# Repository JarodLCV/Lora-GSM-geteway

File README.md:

# **Passerelle LoRa-GSM**  

Un projet combinant des connaissances en électronique et en programmation pour créer un pont entre le GSM et le LoRa.

----

**Table de matières**
- [**Passerelle LoRa-GSM**](#passerelle-lora-gsm)
  - [ℹ️ **Contexte du projet**](#ℹ️-contexte-du-projet)
  - [🗂️ Dossiers](#️-dossiers)
  - [**Réalisation du projet**](#réalisation-du-projet)
    - [**Définitions :**](#définitions-)
  - [Comment continuer le projet](#comment-continuer-le-projet)
  - [Explication du code](#explication-du-code)

----

## ℹ️ **Contexte du projet**

Il s'agit d'un projet du cours de Projet d'Électronique, encadré par Monsieur Christian Peter (<Christian.PETER@univ-cotedazur.fr>), dans le cadre du cursus d'Ingénierie Électronique et Informatique Industrielle de la Polytech de Sophia Antipolis.  
Ce projet consiste à concevoir une ruche connectée, incluant la collecte de données, la transmission de ces données à distance, l’élimination des parasites par laser, etc.  
Cette partie du projet concerne la communication à distance des données et est réalisée par le groupe composé de:
**Guilherme VENTAPANE RODRIGUES** <guilherme@ventapane.eu>
et
**Jarod LECOEUVRE** <jarod.lecoeuvre@etu.univ-cotedazur.fr>

## 🗂️ Dossiers

- 📁 **Compte-rendu** : Les étapes d'avancement du projet et les tâches que chaque membre du groupe avait effectuées.

- 📁 **Partie_Electronique** : Fichiers liés à la partie électronique du projet, tels que le schéma de la carte, la documentation des composants, etc.
  - 📁 **BOM** : Bill of Material de notre projet. La liste des composants nécessaires avec leurs valeurs, pour être placés sur le PCB.
  - 📁 **Documentation_composants** : Fichiers de documentation pour certains composants utilisés dans le projet.
  - 📁 **Eagle_Components** : Composants supplémentaires pour le logiciel EAGLE, qui n'étaient pas présents par défaut et que nous avons dû télécharger pour compléter notre projet.
  - 📁 **Eagle_Schemas** : Schémas que nous avons utilisés pour notre projet, réalisés avec le logiciel EAGLE d'Autodesk.
  - 📁 **Nano to micro simcard adapter 3d** : Un adaptateur de carte SIM vers micro SIM que nous avons imprimé en 3D pour notre projet.
  - 📁 **Anciens_Schemas** : Fichiers de schémas du groupe de l'année dernière.

- 📁 **Partie_Informatique** : Le dossier où se trouve le code qui tourne sur la carte.
  - 📁 **code_groupe_annee_derniere** : Code du projet du groupe de l'année dernière.
  - 📁 **src** : Les fichiers sources de notre projet, où se trouve le fichier main.ino, le fichier principal de notre projet.

## **Réalisation du projet**  

Pour assurer la communication des données sur de longues distances, une passerelle entre LoRa et GSM sera utilisée.  
Cette passerelle sera réalisée à partir d'un circuit imprimé conçu par nous, ainsi que d'un code exécuté sur un **ESP32** connecté à un **SIM7000G**.

Nous nous basons sur le projet de la promotion précédente, réalisé par **Oumar Sadjo Barry & Mor Dieng** / [oumarsadjo / RucherLoRa](https://github.com/oumarsadjo/RucherLoRa)  
<oumar-sadjo.barry@etu.univ-cotedazur.fr> & <mor.dieng@etu.univ-cotedazur.fr>

### **Définitions :**  

**GSM (Global System for Mobile Communications) :**  
C'est un standard de communication mobile utilisé pour la téléphonie cellulaire et la transmission de données. Il permet l’envoi de messages SMS, les appels et la connexion à Internet via **GPRS/EDGE/3G/4G**. Le GSM est largement utilisé pour les dispositifs IoT nécessitant une connectivité dans des environnements sans Wi-Fi.  

**LoRa (Long Range) :**  
C'est une technologie de communication sans fil à longue portée et à faible consommation d'énergie, utilisée pour connecter des dispositifs IoT aux réseaux LPWAN (**Low Power Wide Area Network**). LoRa permet de transmettre de petits paquets de données sur de longues distances (jusqu'à 15 km en zones rurales) avec une consommation d’énergie minimale.  

**ESP32 :**  
C'est un microcontrôleur développé par Espressif, intégrant **Wi-Fi et Bluetooth**, ainsi que plusieurs broches **GPIO** pour les capteurs et modules externes. Il est largement utilisé dans les projets IoT grâce à sa connectivité, sa puissance et son faible coût.  

**SIM7000 :**  
C'est un module de communication **GSM/GPRS/NB-IoT/LTE Cat-M1** développé par Simcom. Il permet aux dispositifs IoT d'envoyer et de recevoir des données via les réseaux mobiles, en prenant en charge les connexions **basse consommation**, idéales pour les capteurs distants et les applications de surveillance.  

## Comment continuer le projet

Il reste encore à :
- [ ] Finaliser le débogage de la carte pour établir une communication stable entre les composants ;
- [ ] Intégrer la partie LoRa ;
- [ ] Optimiser la consommation énergétique de la passerelle, pour un usage autonome sur batterie.

## Explication du code

La bibliothèque utilise la communication série (UART) pour envoyer des commandes AT au module GSM. En interne, elle structure ces commandes de façon organisée, permettant au développeur de simplement appeler des fonctions comme modem.gprsConnect() ou modem.sendSMS(), au lieu d’écrire manuellement des lignes du type `AT+CGDCONT=1`,"IP","internet".

TinyGSM est également optimisée pour fonctionner sur des cartes à faible mémoire (d’où le “Tiny” dans son nom), ce qui la rend efficace même sur des microcontrôleurs limités comme l’Arduino Uno.

Analyse du code et explication des parties principales

Le code de notre projet est organisé en plusieurs étapes : configuration, initialisation du modem, choix des modes réseau, test de la connexion GPRS, et envoi de SMS. Voici un résumé des parties essentielles :

Définition du modem et configuration initiale
Au début du code, on définit le type de modem utilisé :

``` CPP
#define TINY_GSM_MODEM_SIM7000
#define TINY_GSM_RX_BUFFER 1024
#define SerialAT Serial1
```

Ces lignes informent la bibliothèque qu’on utilise un SIM7000. On augmente aussi la taille du buffer de réception à 1024 octets, ce qui est utile pour traiter des réponses longues du modem.

Il y a aussi l’option suivante :

``` CPP
#define DUMP_AT_COMMANDS
```

Cela permet d’afficher toutes les commandes AT envoyées et les réponses reçues. C’est très utile pour déboguer si quelque chose ne fonctionne pas comme prévu.

Paramètres pour le réseau mobile

``` CPP
const char apn[]  = "sl2sfr";
const char gprsUser[] = "";
const char gprsPass[] = "";
```

Ici, on entre les informations nécessaires pour se connecter au réseau mobile. L’APN dépend de l’opérateur utilisé. Dans notre cas, c’est “sl2sfr” car nous utilisons un SIM de SFR.

Initialisation du modem

Dans la fonction setup(), on initialise la communication série avec le modem :

``` CPP
SerialAT.begin(UART_BAUD, SERIAL_8N1, PIN_RX, PIN_TX);
```

Ensuite, on redémarre le modem avec `modem.restart()` et on vérifie si tout s’est bien passé.

On récupère aussi quelques infos utiles :

``` CPP
String name = modem.getModemName();
String modemInfo = modem.getModemInfo();
```

Cela permet d’afficher le nom du modem et quelques infos techniques pour s’assurer que le module est bien reconnu.

Configuration du mode réseau

Dans la `loop()`, on configure le mode de fonctionnement du modem :

``` CPP
modem.sendAT("+CFUN=0"); // désactive le modem temporairement
modem.setNetworkMode(2); // mode automatique
modem.setPreferredMode(1); // priorité au mode CAT-M
modem.sendAT("+CFUN=1"); // réactive le modem
```

Ces commandes AT permettent de choisir comment le modem va chercher le réseau (LTE, GSM, NB-IoT, etc.).

Connexion GPRS

Une fois le modem prêt, on tente de se connecter au réseau mobile :

``` CPP
modem.gprsConnect(apn, gprsUser, gprsPass);
```

Après la connexion, on peut vérifier le signal, l’opérateur, l’IMEI, l’adresse IP locale, etc.

Envoi de SMS

À la fin du code, il y a une partie pour tester l’envoi de SMS :

``` CPP
modem.sendSMS(SMS_TARGET, String("Hello from ") + imei);
```

C’est un test simple qui envoie un message contenant l’IMEI du module à un numéro prédéfini.

Mise hors tension et sommeil profond

Enfin, on met le modem hors tension et on fait entrer l’ESP32 en mode sommeil profond pour économiser l’énergie :

``` CPP
modem.poweroff();
esp_deep_sleep_start();
```

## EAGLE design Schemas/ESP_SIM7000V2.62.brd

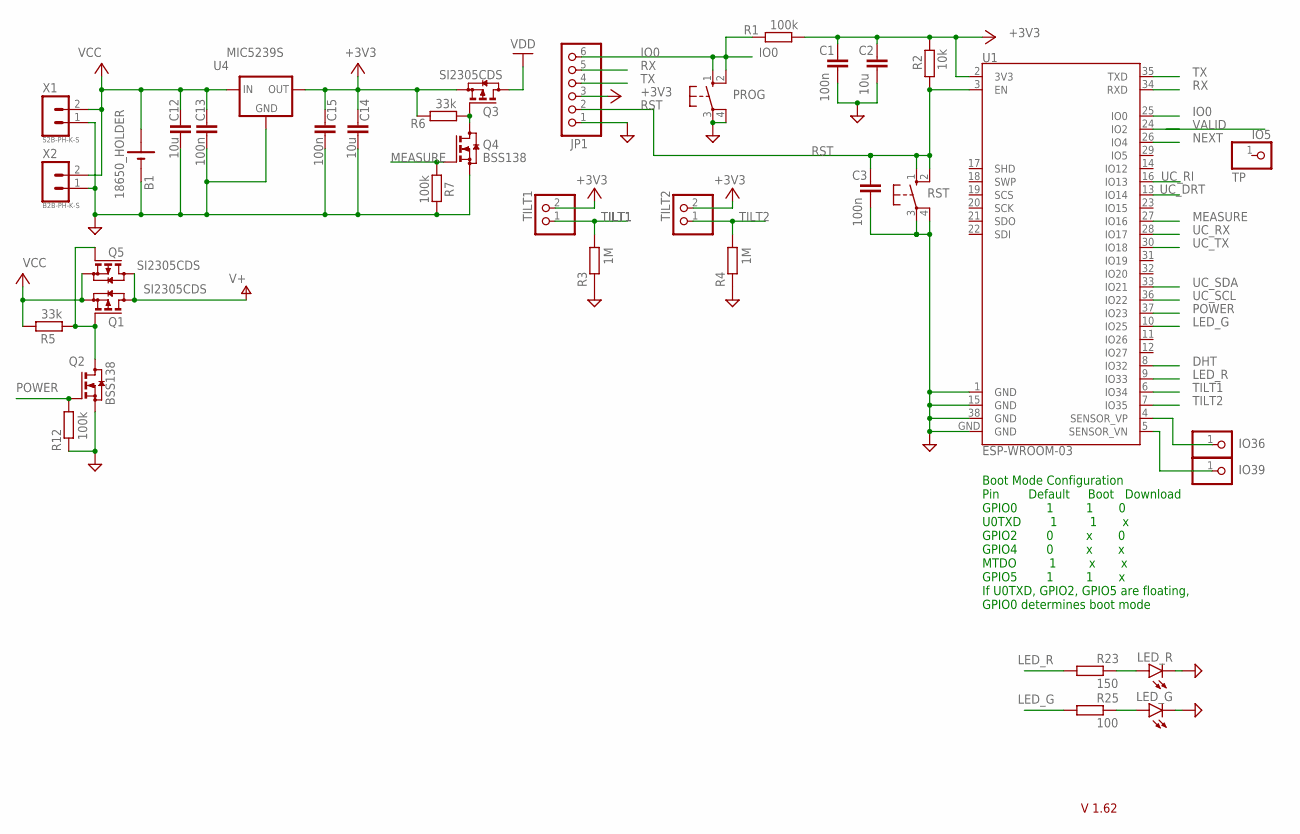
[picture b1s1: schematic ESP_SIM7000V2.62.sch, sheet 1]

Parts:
B1: 18650_HOLDER; 18650
C1, C3, C13, C15: 100n; C1206
C2, C12, C14: 10u; C1210
IO5: TP; 1X01
IO36, IO39: PINHD-1X1; 1X01
JP1: PINHD-1X6; 1X06
LED_G: LEDSMT1206; 1206
LED_R: LEDSMT1206; 1206
PROG: 10-XX; B3F-10XX
Q1, Q3, Q5: SI2305CDS; SOT23
Q2, Q4: BSS138; SOT23
R1, R7, R12: 100k; R1206
R2: 10k; R1206
R3, R4: 1M; R1206
R5, R6: 33k; R1206
R23: 150; R1206
R25: 100; R1206
RST: 10-XX; B3F-10XX
TILT1, TILT2: PINHD-1X2; 1X02
U1: ESP-WROOM-03
U4: MIC5239S; SOT223
X1: S2B-PH-K-S
X2: B2B-PH-K-S

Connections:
+3V3: C1.1, C2.1, C14.1, C15.1, JP1.3, Q3.2 (S), R1.1, R2.2, R6.2, TILT1.2, TILT2.2, U1.2 (3V3), U4.3 (OUT); also elsewhere on the board
DHT: U1.8 (IO32)
GND: B1.-, C1.2, C2.2, C3.2, C12.2, C13.2, C14.2, C15.2, JP1.1, LED_G.C, LED_R.C, PROG.3, PROG.4 (P1), Q2.2 (S), Q4.2 (S), R3.2, R4.2, R7.2, R12.2, RST.3, RST.4 (P1), U1.1 (GND), U1.15 (GND), U1.38 (GND), U1.GND, U4.2 (GND), U4.4 (GND), X1.1, X2.1; also elsewhere on the board
IO0: JP1.6, PROG.1 (S), PROG.2 (S1), R1.2, U1.25 (IO0)
IO36: IO36.1, U1.4 (SENSOR_VP)
IO39: IO39.1, U1.5 (SENSOR_VN)
LED_G: R25.1, U1.10 (IO25)
LED_R: R23.1, U1.9 (IO33); also elsewhere on the board
MEASURE: Q4.1 (G), R7.1, U1.27 (IO16)
unnamed: Q1.1 (G), Q2.3 (D), Q5.1 (G), R5.1
unnamed: Q3.1 (G), Q4.3 (D), R6.1
unnamed: LED_R.A, R23.2
unnamed: LED_G.A, R25.2
unnamed: IO5.1, U1.29 (IO5)
NEXT: U1.26 (IO4)
POWER: Q2.1 (G), R12.1, U1.37 (IO23)
RST: C3.1, JP1.2, R2.1, RST.1 (S), RST.2 (S1), U1.3 (EN)
RX: JP1.5, U1.34 (RXD)
TILT1: R3.1, TILT1.1, U1.6 (IO34)
TILT2: R4.1, TILT2.1, U1.7 (IO35)
TX: JP1.4, U1.35 (TXD)
UC_DRT: U1.13 (IO14); also elsewhere on the board
UC_RI: U1.16 (IO13); also elsewhere on the board
UC_RX: U1.28 (IO17); also elsewhere on the board
UC_SCL: U1.36 (IO22); also elsewhere on the board
UC_SDA: U1.33 (IO21); also elsewhere on the board
UC_TX: U1.30 (IO18); also elsewhere on the board
V+: Q1.3 (D), Q5.3 (D); also elsewhere on the board
VALID: U1.24 (IO2)
VCC: B1.+, C12.1, C13.1, Q1.2 (S), Q5.2 (S), R5.2, U4.1 (IN), X1.2, X2.2
VDD: Q3.3 (D)

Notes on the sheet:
Boot Mode Configuration Pin Default Boot Download GPIO0 1 1 0 U0TXD 1 1 x GPIO2 0 x 0 GPIO4 0 x x MTDO 1 x x GPIO5 1 1 x If U0TXD, GPIO2, GPIO5 are floating, GPIO0 determines boot mode
V 1.62

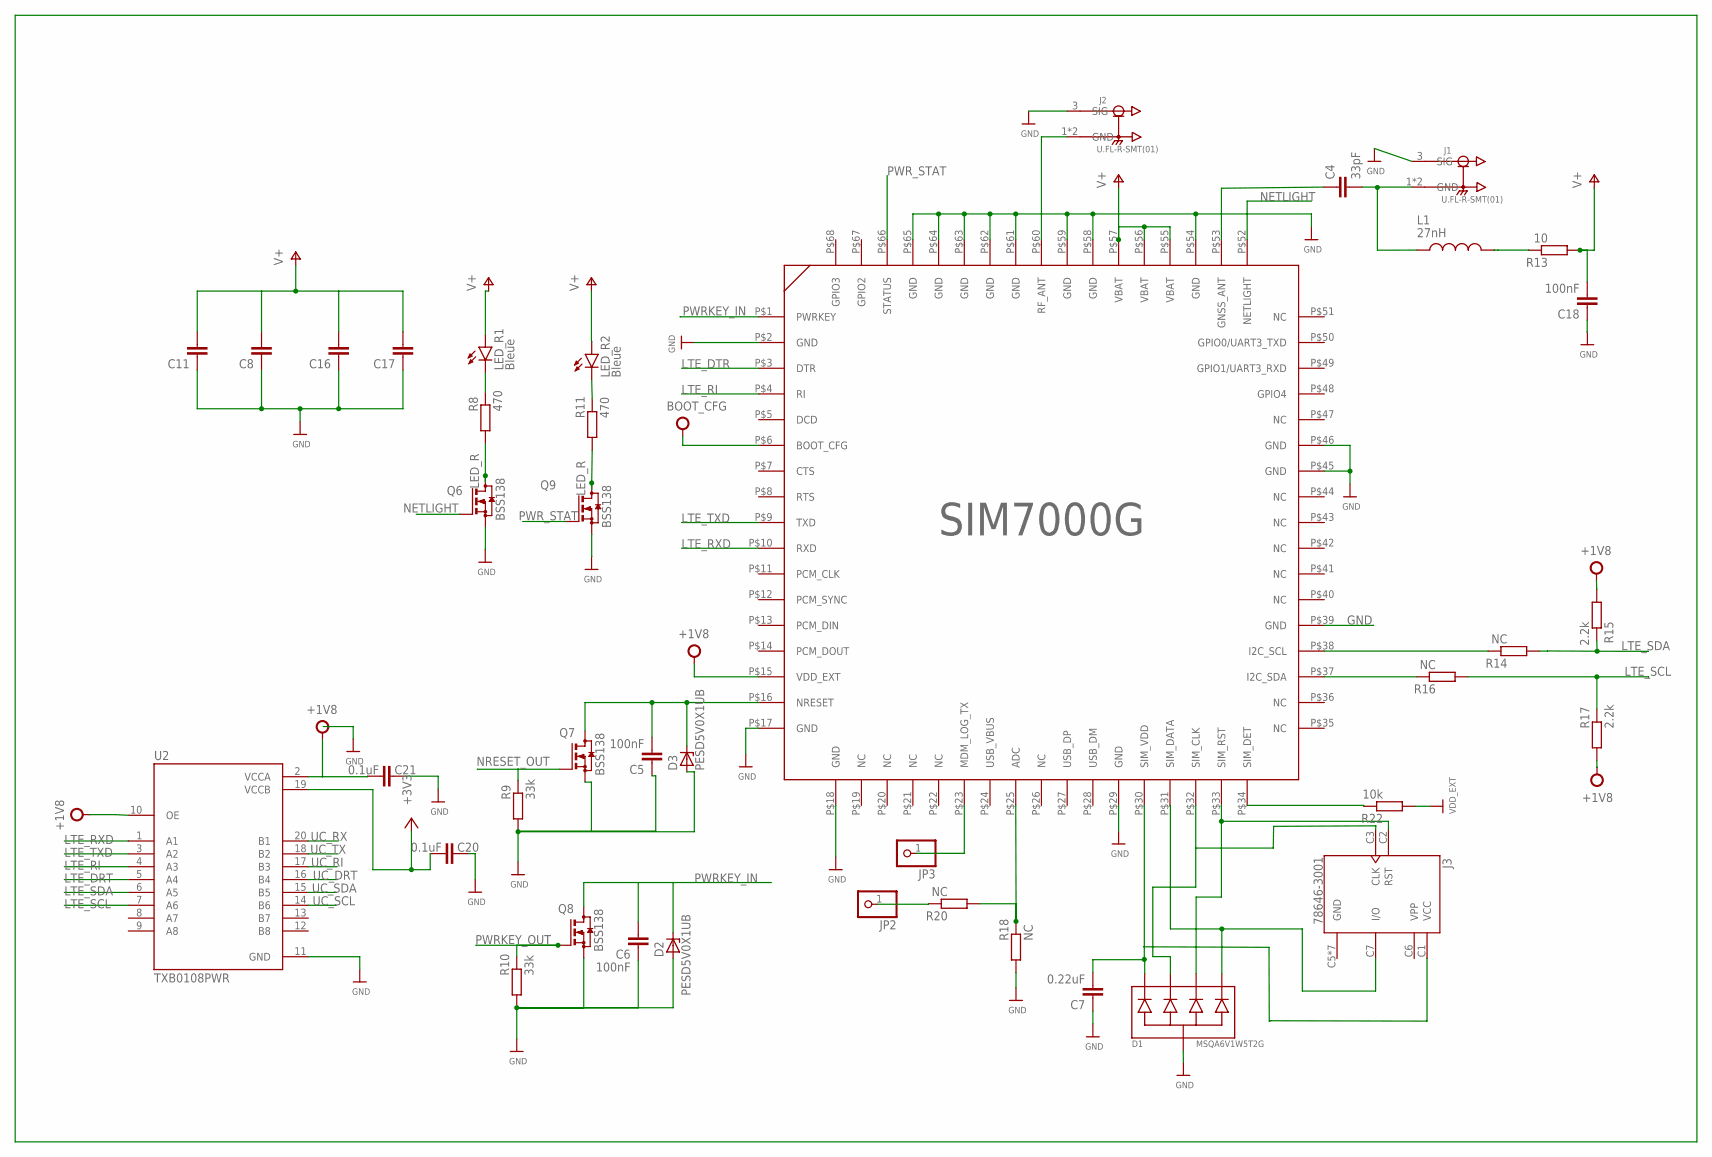
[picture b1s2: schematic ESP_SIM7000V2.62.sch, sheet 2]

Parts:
C4: 33pF; C0805
C5, C6, C18: 100nF; C0805
C7: 0.22uF; C0805
C8: 1uF; C0805
C11: 0.1uF; C0805
C16, C17: 100uF; C0805
C20, C21: 0.1uF; C1210
D1: MSQA6V1W5T2G; SC88A
D2, D3: PESD5V0X1UB; SOD523
J1, J2: U.FL-R-SMT(01); HRS_U.FL-R-SMT(01)
J3: 78646-3001; MOLEX_78646-3001
JP2, JP3: PINHD-1X1; 1X01
L1: 27nH; INDC2012X100N
LED_R1, LED_R2: Bleue; 1206
Q6, Q7, Q8, Q9: BSS138; SOT23
R8, R11: 470; R1206
R9, R10: 33k; R1206
R13: 10; R1206
R14, R16, R18, R20: NC; R1206
R15, R17: 2.2k; R1206
R22: 10k; R1206
U2: TXB0108PWR; SOP65P640X120-20N
U$1: SIM7000G

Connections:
+1V8: C21.2, R15.1, R17.1, U2.2 (VCCA), U2.10 (OE), U$1.P$6 (BOOT_CFG), U$1.P$15 (VDD_EXT)
+3V3: C20.2, U2.19 (VCCB); also elsewhere on the board
GND: C5.1, C6.1, C7.1, C8.1, C11.1, C16.1, C17.1, C18.1, C20.1, C21.1, D1.2, D2.2 (A), D3.2 (A), J1.3 (SIG), J2.3 (SIG), J3.C5 (GND), J3.G1 (GND), J3.G2 (GND), J3.G3 (GND), J3.G4 (GND), J3.G5 (GND), J3.G6 (GND), Q6.2 (S), Q7.2 (S), Q8.2 (S), Q9.2 (S), R9.1, R10.1, R18.1, R22.1, U2.11 (GND), U$1.P$2 (GND), U$1.P$17 (GND), U$1.P$18 (GND), U$1.P$29 (GND), U$1.P$39 (GND), U$1.P$45 (GND), U$1.P$46 (GND), U$1.P$54 (GND), U$1.P$58 (GND), U$1.P$59 (GND), U$1.P$61 (GND), U$1.P$62 (GND), U$1.P$63 (GND), U$1.P$64 (GND), U$1.P$65 (GND); also elsewhere on the board
LED_R: Q6.3 (D), Q9.3 (D), R8.1, R11.1; also elsewhere on the board
LTE_DRT: U2.5 (A4)
LTE_DTR: U$1.P$3 (DTR)
LTE_RI: U2.4 (A3), U$1.P$4 (RI)
LTE_RXD: U2.1 (A1), U$1.P$10 (RXD)
LTE_SCL: R16.1, R17.2, U2.7 (A6)
LTE_SDA: R14.1, R15.2, U2.6 (A5)
LTE_TXD: U2.3 (A2), U$1.P$9 (TXD)
unnamed: J2.1 (GND), J2.2 (GND), U$1.P$60 (RF_ANT)
unnamed: C4.2, J1.1 (GND), J1.2 (GND), L1.1
unnamed: C4.1, U$1.P$53 (GNSS_ANT)
unnamed: C5.2, D3.1 (K), Q7.3 (D), U$1.P$16 (NRESET)
unnamed: LED_R1.C, R8.2
unnamed: D1.5, J3.C7 (I/O), U$1.P$31 (SIM_DATA)
unnamed: D1.4, J3.C2 (RST), U$1.P$33 (SIM_RST)
unnamed: JP2.1, R20.2
unnamed: LED_R2.C, R11.2
unnamed: R22.2, U$1.P$34 (SIM_DET)
unnamed: L1.2, R13.2
unnamed: D1.3, U$1.P$32 (SIM_CLK)
unnamed: R14.2, U$1.P$38 (I2C_SCL)
unnamed: R16.2, U$1.P$37 (I2C_SDA)
unnamed: C7.2, D1.1, U$1.P$30 (SIM_VDD)
unnamed: R18.2, R20.1, U$1.P$25 (ADC)
unnamed: JP3.1, U$1.P$23 (MDM_LOG_TX)
NETLIGHT: Q6.1 (G), U$1.P$52 (NETLIGHT)
NRESET_OUT: Q7.1 (G), R9.2
PWRKEY_IN: C6.2, D2.1 (K), Q8.3 (D), U$1.P$1 (PWRKEY)
PWRKEY_OUT: Q8.1 (G), R10.2
PWR_STAT: Q9.1 (G), U$1.P$66 (STATUS)
UC_DRT: U2.16 (B4); also elsewhere on the board
UC_RI: U2.17 (B3); also elsewhere on the board
UC_RX: U2.20 (B1); also elsewhere on the board
UC_SCL: U2.14 (B6); also elsewhere on the board
UC_SDA: U2.15 (B5); also elsewhere on the board
UC_TX: U2.18 (B2); also elsewhere on the board
V+: C8.2, C11.2, C16.2, C17.2, C18.2, LED_R1.A, LED_R2.A, R13.1, U$1.P$55 (VBAT), U$1.P$56 (VBAT), U$1.P$57 (VBAT); also elsewhere on the board
VPP: J3.C6 (VPP)

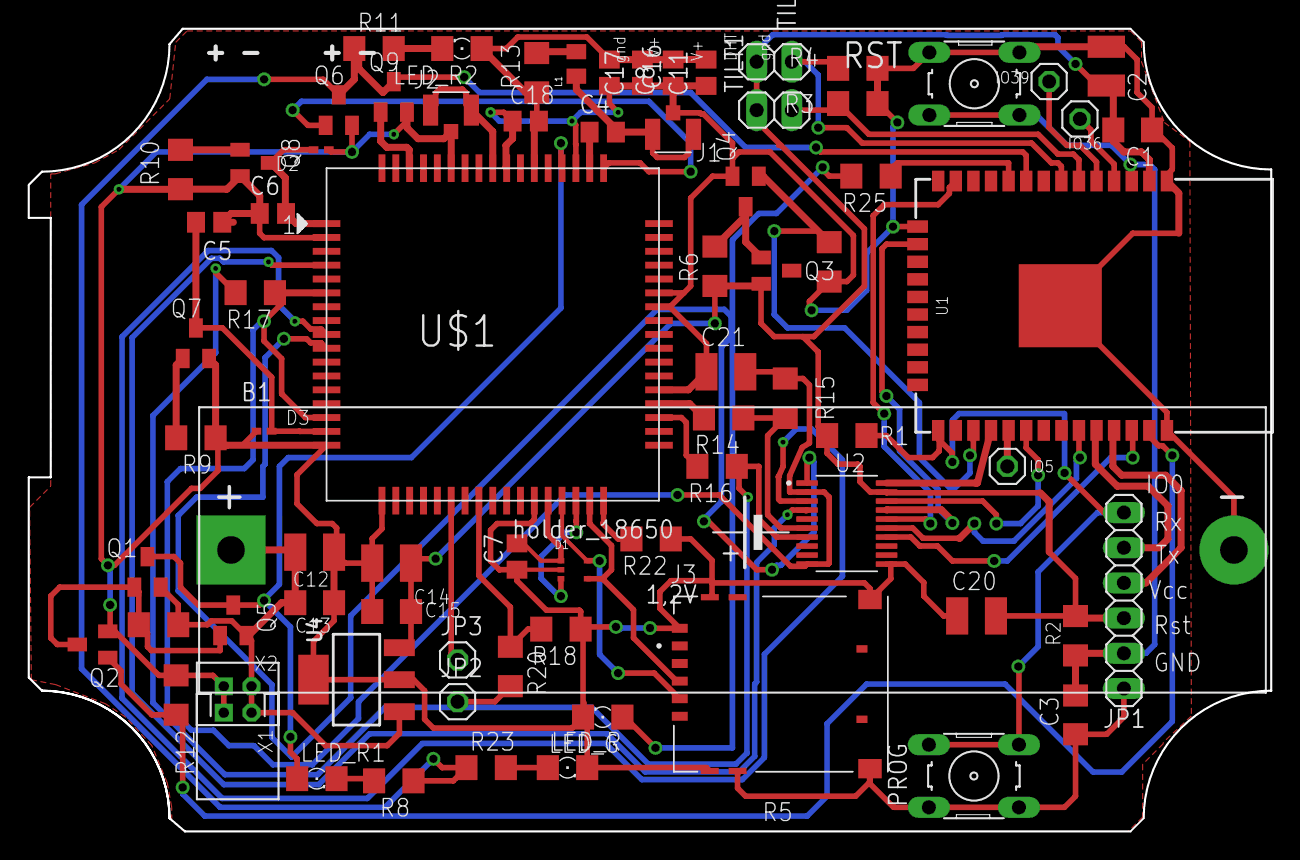
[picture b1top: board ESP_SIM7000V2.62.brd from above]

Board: 2 copper layers, 89.7 x 57.9 mm, 77 parts (0 on the bottom side), 55 nets.

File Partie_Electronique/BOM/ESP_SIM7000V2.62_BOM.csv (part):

"Part";"Value";"Device";"Package";"Description";"AVAILABILITY";"CHECK_PRICES";"DESCRIPTION";"DIGIKEY_PART_NUMBER";"MF";"MP";"MPN";"OC_FARNELL";"OC_NEWARK";"PACKAGE";"POPULARITY";"PRICE";"PURCHASE-URL";"RS_COMPONENTS_1674235_PURCHASE_URL";"RS_COMPONENTS_7099038P_PURCHASE_URL";"RS_COMPONENTS_7099038_PURCHASE_URL";"RS_COMPONENTS_7867096P_PURCHASE_URL";"RS_COMPONENTS_7867096_PURCHASE_URL";"RS_COMPONENTS_9215119_PURCHASE_URL";"SNAPEDA_LINK";"SPICEMODEL";"SPICEPREFIX";
"B1";"18650_HOLDER";"18650_HOLDER";"18650";"18650 holder";"";"";"";"";"";"";"";"";"";"";"";"";"";"";"";"";"";"";"";"";"";"";
"C1";"100n";"CC1206";"C1206";"CAPACITOR, European symbol";"";"";"";"";"";"";"";"";"";"";"";"";"";"";"";"";"";"";"";"";"NONE";"C";
"C2";"10u";"CC1210";"C1210";"CAPACITOR, European symbol";"";"";"";"";"";"";"";"";"";"";"";"";"";"";"";"";"";"";"";"";"NONE";"C";
"C3";"100n";"CC1206";"C1206";"CAPACITOR, European symbol";"";"";"";"";"";"";"";"";"";"";"";"";"";"";"";"";"";"";"";"";"NONE";"C";
"C4";"33pF";"C-EUC0805";"C0805";"CAPACITOR, European symbol";"";"";"";"";"";"";"";"";"";"";"88";"";"";"";"";"";"";"";"";"";"";"C";
"C5";"100nF";"C-EUC0805";"C0805";"CAPACITOR, European symbol";"";"";"";"";"";"";"";"";"";"";"88";"";"";"";"";"";"";"";"";"";"";"C";
"C6";"100nF";"C-EUC0805";"C0805";"CAPACITOR, European symbol";"";"";"";"";"";"";"";"";"";"";"88";"";"";"";"";"";"";"";"";"";"";"C";
"C7";"0.22uF";"C-EUC0805";"C0805";"CAPACITOR, European symbol";"";"";"";"";"";"";"";"";"";"";"88";"";"";"";"";"";"";"";"";"";"";"C";
"C8";"1uF";"C-EUC0805";"C0805";"CAPACITOR, European symbol";"";"";"";"";"";"";"";"";"";"";"88";"";"";"";"";"";"";"";"";"";"";"C";
"C11";"0.1uF";"C-EUC0805";"C0805";"CAPACITOR, European symbol";"";"";"";"";"";"";"";"";"";"";"88";"";"";"";"";"";"";"";"";"";"";"C";
"C12";"10u";"CC1210";"C1210";"CAPACITOR, European symbol";"";"";"";"";"";"";"";"";"";"";"";"";"";"";"";"";"";"";"";"";"NONE";"C";
"C13";"100n";"CC1206";"C1206";"CAPACITOR, European symbol";"";"";"";"";"";"";"";"";"";"";"";"";"";"";"";"";"";"";"";"";"NONE";"C";
"C14";"10u";"CC1210";"C1210";"CAPACITOR, European symbol";"";"";"";"";"";"";"";"";"";"";"";"";"";"";"";"";"";"";"";"";"NONE";"C";
"C15";"100n";"CC1206";"C1206";"CAPACITOR, European symbol";"";"";"";"";"";"";"";"";"";"";"";"";"";"";"";"";"";"";"";"";"NONE";"C";
"C16";"100uF";"C-EUC0805";"C0805";"CAPACITOR, European symbol";"";"";"";"";"";"";"";"";"";"";"88";"";"";"";"";"";"";"";"";"";"";"C";
"C17";"100uF";"C-EUC0805";"C0805";"CAPACITOR, European symbol";"";"";"";"";"";"";"";"";"";"";"88";"";"";"";"";"";"";"";"";"";"";"C";
"C18";"100nF";"C-EUC0805";"C0805";"CAPACITOR, European symbol";"";"";"";"";"";"";"";"";"";"";"88";"";"";"";"";"";"";"";"";"";"";"C";
"C20";"0.1uF";"CC1210";"C1210";"CAPACITOR, European symbol";"";"";"";"";"";"";"";"";"";"";"";"";"";"";"";"";"";"";"";"";"NONE";"C";
"C21";"0.1uF";"CC1210";"C1210";"CAPACITOR, European symbol";"";"";"";"";"";"";"";"";"";"";"";"";"";"";"";"";"";"";"";"";"NONE";"C";
"D1";"MSQA6V1W5T2G";"MSQA6V1W5T2G";"SC88A";"ESD Protection Diode Array  Check availability";"In Stock";"https://www.snapeda.com/parts/MSQA6V1W5T2G/Onsemi/view-part/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";" Clamp Ipp Tvs Diode Surface Mount SC-88A (SC-70-5/SOT-353) ";"";"onsemi";"MSQA6V1W5T2G";"";"";"";"SC-88A-5 ON Semiconductor";"";"None";"https://www.snapeda.com/api/url_track_click_mouser/?unipart_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";"";"";"";"";"";"";"https://www.snapeda.com/parts/MSQA6V1W5T2G/Onsemi/view-part/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";"";"";
"D2";"PESD5V0X1UB";"PESD5V0X1UB";"SOD523";"Ultra low capacitance unidirectional ElectroStatic Discharge (ESD) protection diode in a";"In Stock";"https://www.snapeda.com/parts/PESD5V0X1UB/Nexperia/view-part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";" 8V (Typ) Clamp 1.5A (8/20µs) Ipp Tvs Diode Surface Mount SOD-523 ";"";"Nexperia USA";"PESD5V0X1UB";"";"";"";"SOD-523 NXP Semiconductors";"";"None";"";"";"";"";"";"";"";"https://www.snapeda.com/parts/PESD5V0X1UB/Nexperia/view-part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";"";"";
"D3";"PESD5V0X1UB";"PESD5V0X1UB";"SOD523";"Ultra low capacitance unidirectional ElectroStatic Discharge (ESD) protection diode in a";"In Stock";"https://www.snapeda.com/parts/PESD5V0X1UB/Nexperia/view-part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";" 8V (Typ) Clamp 1.5A (8/20µs) Ipp Tvs Diode Surface Mount SOD-523 ";"";"Nexperia USA";"PESD5V0X1UB";"";"";"";"SOD-523 NXP Semiconductors";"";"None";"";"";"";"";"";"";"";"https://www.snapeda.com/parts/PESD5V0X1UB/Nexperia/view-part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";"";"";
"IO5";"TP";"PINHD-1X1";"1X01";"PIN HEADER";"";"";"";"";"";"";"";"";"";"";"64";"";"";"";"";"";"";"";"";"";"";"";
"IO36";"";"PINHD-1X1";"1X01";"PIN HEADER";"";"";"";"";"";"";"";"";"";"";"64";"";"";"";"";"";"";"";"";"";"";"";
"IO39";"";"PINHD-1X1";"1X01";"PIN HEADER";"";"";"";"";"";"";"";"";"";"";"64";"";"";"";"";"";"";"";"";"";"";"";
"J1";"U.FL-R-SMT(01)";"U.FL-R-SMT(01)";"HRS_U.FL-R-SMT(01)";"U.FL Series 6 Ghz 50 Ohm Ultra-small SMT Coaxial Cable Receptacle Check availability";"In Stock";"https://www.snapeda.com/parts/U.FL-R-SMT(01)/Hirose+Electric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";" U.FL (UMCC) Connector Receptacle, Male Pin 50Ohm Surface Mount Solder. RF Connectors / Coaxial Connectors ";"";"Hirose";"U.FL-R-SMT(01)";"";"";"";"None";"";"None";"https://www.snapeda.com/api/url_track_click_mouser/?unipart_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";"";"";"";"";"";"";"https://www.snapeda.com/parts/U.FL-R-SMT(01)/Hirose+Electric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";"";"";
"J2";"U.FL-R-SMT(01)";"U.FL-R-SMT(01)";"HRS_U.FL-R-SMT(01)";"U.FL Series 6 Ghz 50 Ohm Ultra-small SMT Coaxial Cable Receptacle Check availability";"In Stock";"https://www.snapeda.com/parts/U.FL-R-SMT(01)/Hirose+Electric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";" U.FL (UMCC) Connector Receptacle, Male Pin 50Ohm Surface Mount Solder. RF Connectors / Coaxial Connectors ";"";"Hirose";"U.FL-R-SMT(01)";"";"";"";"None";"";"None";"https://www.snapeda.com/api/url_track_click_mouser/?unipart_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";"";"";"";"";"";"";"https://www.snapeda.com/parts/U.FL-R-SMT(01)/Hirose+Electric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";"";"";
"J3";"78646-3001";"78646-3001";"MOLEX_78646-3001";"Conn Micro SIM Card SKT 6 POS 2.54mm Solder RA SMD 0.5A/Contact Embossed T/R Check availability";"In Stock";"https://www.snapeda.com/parts/78646-3001/Molex/view-part/?ref=eda";" Horizontal Surface Mount Micro SIM Card Connector, with Push In Termination | Molex Incorporated 78646-3001 ";"";"Molex";"78646-3001";"";"";"";"None";"";"None";"https://www.snapeda.com/api/url_track_click_mouser/?unipart_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 sim";"";"";"";"";"";"";"https://www.snapeda.com/parts/78646-3001/Molex/view-part/?ref=snap";"";"";
"JP1";"";"PINHD-1X6";"1X06";"PIN HEADER";"";"";"";"";"";"";"";"";"";"";"79";"";"";"";"";"";"";"";"";"";"";"";
"JP2";"";"PINHD-1X1";"1X01";"PIN HEADER";"";"";"";"";"";"";"";"";"";"";"64";"";"";"";"";"";"";"";"";"";"";"";
"JP3";"";"PINHD-1X1";"1X01";"PIN HEADER";"";"";"";"";"";"";"";"";"";"";"64";"";"";"";"";"";"";"";"";"";"";"";
"L1";"27nH";"LQM21PN1R0NGRD";"INDC2012X100N";"LQM21PN 1uH 950mA 30% MLT";"";"https://www.snapeda.com/parts/LQM21PN1R0NGRD/Murata+Electron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";" Inductor with Inductance: 1uH Tol. +/-30%, Package: 0805 (2012) ";"";"Murata";"LQM21PN1R0NGRD";"";"";"";"2012 Murata";"";"";"https://www.snapeda.com/api/url_track_click_mouser/?unipart_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 0805";"https://www.snapeda.com/api/url_track_click/https%253A//uk.r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 0805";"";"";"https://www.snapeda.com/api/url_track_click/https%253A//uk.r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 0805";"https://www.snapeda.com/api/url_track_click/https%253A//uk.r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 0805";"";"https://www.snapeda.com/parts/LQM21PN1R0NGRD/Murata+Electron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";"";"";
"LED_G";"";"LEDSMT1206";"1206";"LED";"";"";"";"";"";"";"";"";"";"";"20";"";"";"";"";"";"";"";"";"";"";"";
"LED_R";"";"LEDSMT1206";"1206";"LED";"";"";"";"";"";"";"";"";"";"";"20";"";"";"";"";"";"";"";"";"";"";"";
"LED_R1";"Bleue";"LEDSMT1206";"1206";"LED";"";"";"";"";"";"";"";"";"";"";"20";"";"";"";"";"";"";"";"";"";"";"";
"LED_R2";"Bleue";"LEDSMT1206";"1206";"LED";"";"";"";"";"";"";"";"";"";"";"20";"";"";"";"";"";"";"";"";"";"";"";
"PROG";"";"10-XX";"B3F-10XX";"OMRON SWITCH";"";"";"";"";"";"";"B3F-1000";"176432";"36M3542";"";"72";"";"";"";"";"";"";"";"";"";"";"";
"Q1";"SI2305CDS";"SI2305CDS";"SOT23";"P-CHANNEL MOS FET";"";"";"";"";"";"";"";"";"";"";"";"";"";"";"";"";"";"";"";"";"";"";
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
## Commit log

2024-09-23 Create salut
2024-09-23 Add README.md with project name
2024-09-23 Create file for compte-rendu
2024-09-23 Compte rendu
2024-11-25 Update Guilherme.md
    Rajouté une ligne j'avais oublié
2024-11-25 test
2024-11-25 Rajout de la documentation et des schémas.
2024-11-25 Fichiers et dossiers
2024-11-25 Dossiers
2024-11-25 Rajout composants Eagle
2024-11-25 Rajout documentation composants
2024-11-25 Modifs compte rendu
2024-11-25 Compte rendu du 25 novembre
2024-11-26 Rajouté GitIgnore
2024-11-26 Enlevé des fichiers non necessaires
2024-11-26 Update cahier de charges
2024-11-28 Modifs
2024-11-28 resolution problem
2024-11-28 resolution 2
2024-12-05 Update Changelog
2024-12-05 Rajouté "TODO"
2024-12-05 Update Guilherme.md avec les images des erreurs.
2024-12-05 Plus de détails sur l'avancement
2024-12-05 Rajouté le l'URL de la formation EAGLE j'ai suivi.
2024-12-05 Correction de mes erreurs de Français
2024-12-05 Rajouté les jours de semaine
2024-12-11 Modifs compte rendu et correction
2025-01-07 26 nov + 09 dec
2025-01-07 Updated Guilherme.md
2025-01-31 Mouvement, voiture aléatoires, deux types de NPC...
2025-01-31 Cablage
2025-02-02 Avancement
2025-02-02 Routage
2025-02-03 Modifs EAGLE et Compte rendu
2025-02-03 compte rendu 3/02
2025-02-03 Update Guilherme.md image avec mes modifs et modifs Jarod
2025-02-07 PCB OK
2025-02-25 Réussi à faire fonctionner le code pour communiquer l'ESP32 avec la SIM7000G.
2025-02-26 Ajouté le code de l'année dernière pour faire des essais.
2025-02-28 Gitignore de DS_Store
2025-03-11 Fait marcher la carte et envoyer le SMS, voir "codeQuiFonctionneTropBien.ino"
2025-03-24 last version
2025-04-11 Add rapport and 3d sim
2025-04-14 Compte rendu Guilherme
2025-04-14 Déplacé les fichiers de la carte SIM pour mieux organiser les dossiers de notre projet.
2025-04-14 Déplacé dossiers
2025-04-14 Réorganisé tous les dossiers du projet.
2025-05-17 Passage du code en Français
2025-05-17 Enlevé la partie du code qui ne sert pas à notre projet
2025-05-18 Modifications README.md, nom dossier, ajout compte rendu Jarod
2025-05-18 Modifs dans README.md
2025-05-18 Ajout du compte rendu

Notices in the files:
parts and their libraries:
micrel: Copyright (C) 2008, Bob Starr
